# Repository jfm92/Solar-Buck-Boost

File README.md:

#Solar Buck-Boost

Li-Po charging module with CN3063 and TPS63020 for solar and USB power, ensures constant voltage and efficiency. By default it's configure to ouput 3.3v with power saving mode off.

**Important you can use a solar panel with a maximum of 6V and minimum of 4.4v, but it's recommendable to use 5V solar panel modules**

## Configuration:

This modules allows to set the output voltage an working mode by doing some little modifications.

## Output Voltage:

This module allows to set an ouput voltage by changing R4 resistor. By default it's 1M giving an ouput of 3.3v, but you can get the following ouput values.

| VOUT  |   R4   |
|-------|--------|
| 2.5V  | 750K   |
| 3.3V  | 1M     |
| 3.6V  | 1.1M   |
| 4.5V  | 1.43M  |
| 5V    | 1.6M   |

## Power saving mode:

- Power saving mode on: Join R8.
- Power saving mode off: Join R7.

## Schematics:

## PCB:

## Bill of materials:

You can find a list of material with a link to the crucial one.

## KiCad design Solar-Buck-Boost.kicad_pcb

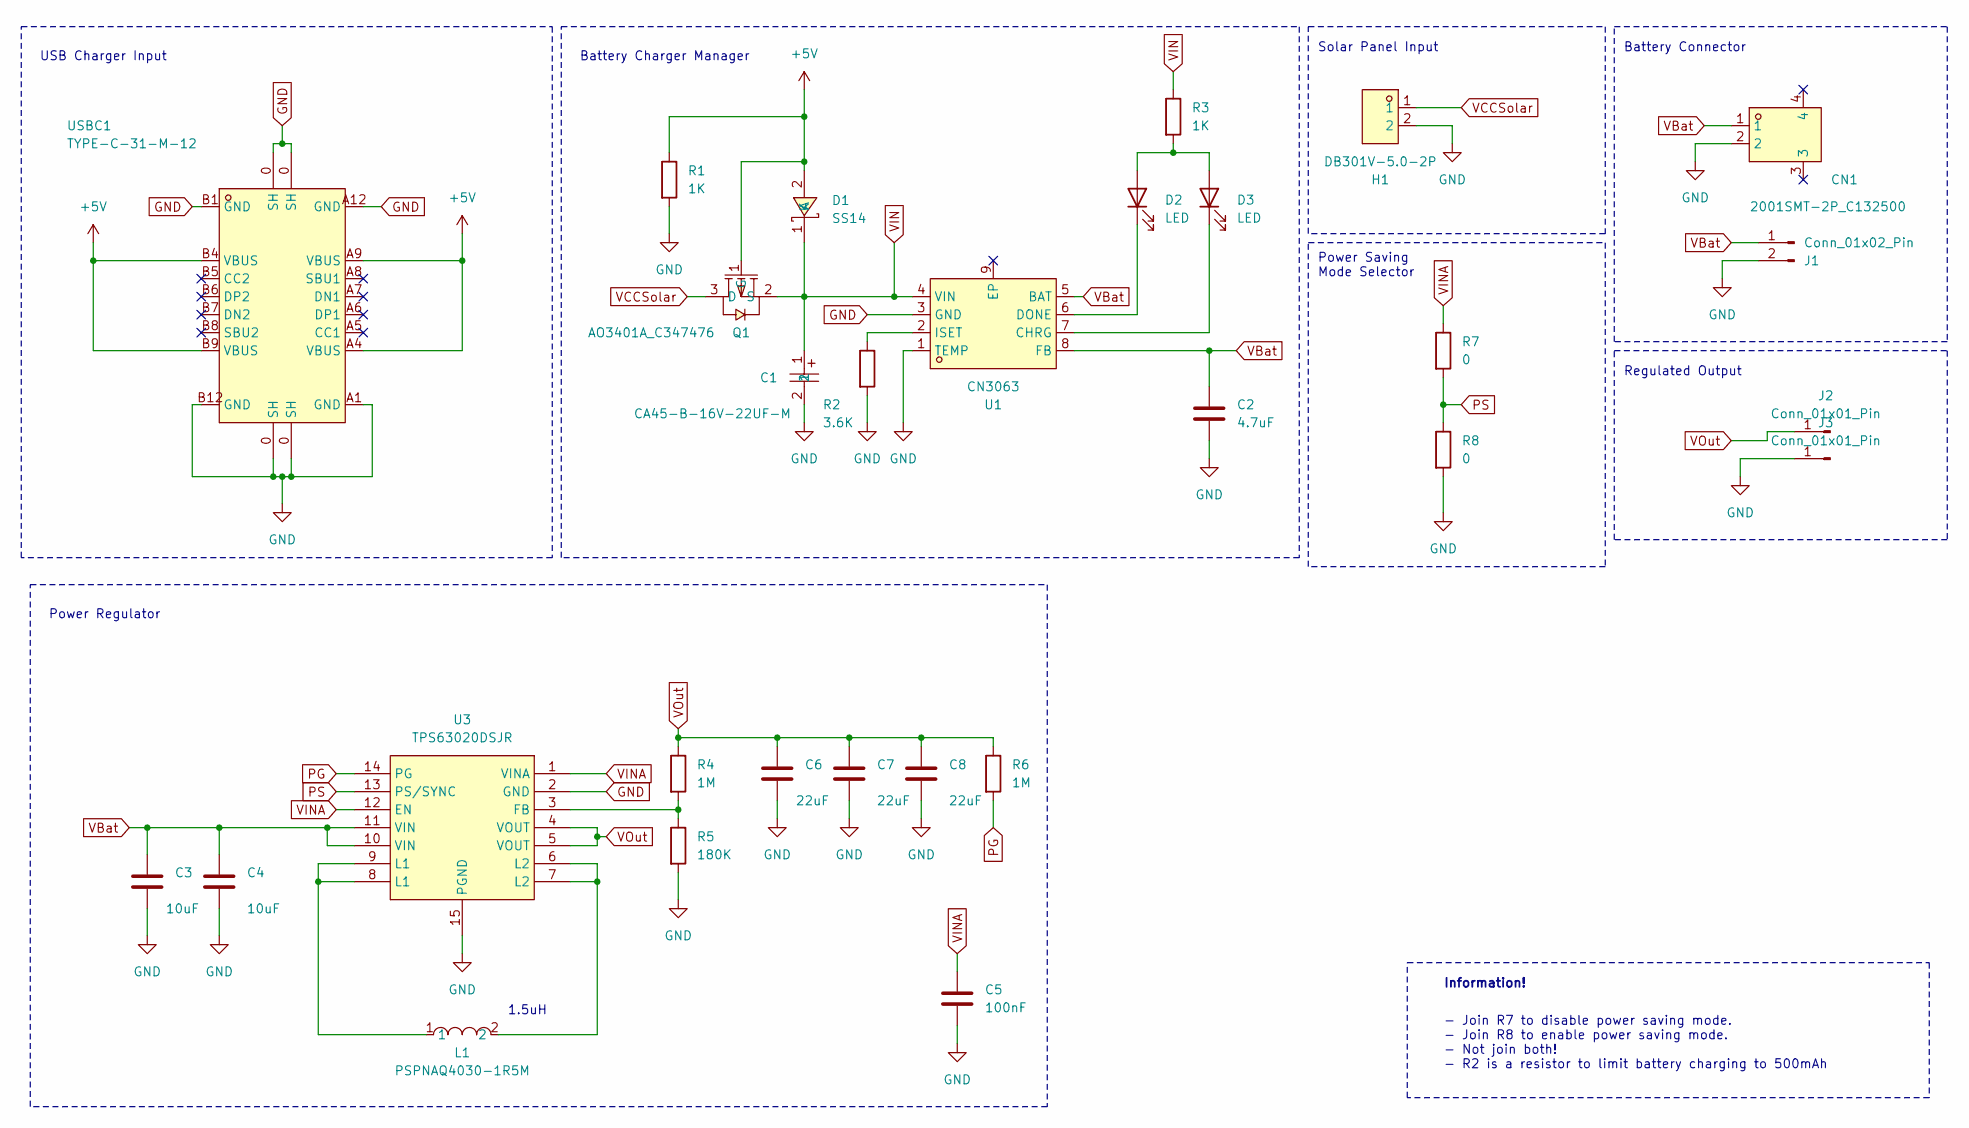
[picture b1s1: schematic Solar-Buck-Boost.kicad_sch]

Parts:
C1: CA45-B-16V-22UF-M; CAP-SMD_L3.5-W2.8-R-RD; LCSC Part C140371
C2: 4.7uF; C_0805_2012Metric
C3, C4: 10uF; C_0805_2012Metric
C5: 100nF; C_0603_1608Metric
C6, C7, C8: 22uF; C_0805_2012Metric
CN1: 2001SMT-2P_C132500; CONN-SMD_2001SMT-2P-WT; LCSC Part C132500
D1: SS14; SMA_L4.2-W2.6-LS5.3-RD; LCSC Part C2480
D2, D3: LED; LED_0805_2012Metric
H1: DB301V-5.0-2P; CONN-TH_2P-P5.00_L7.6-W10.0; LCSC Part C395882
J1: Conn_01x02_Pin; PinHeader_1x02_P2.54mm_Vertical
J2, J3: Conn_01x01_Pin; PinSocket_1x01_P2.54mm_Vertical
L1: PSPNAQ4030-1R5M; IND-SMD_L4.0-W4.0; LCSC Part C436670
Q1: AO3401A_C347476; SOT-23_L2.9-W1.3-P1.90-LS2.4-BR; LCSC Part C347476
R1, R3: 1K; R_0805_2012Metric
R2: 3.6K; R_0805_2012Metric
R4, R6: 1M; R_0805_2012Metric
R5: 180K; R_0805_2012Metric
R7, R8: 0; R_0402_1005Metric
U1: CN3063; SOIC-8_L4.9-W3.9-P1.27-LS6.0-BL-EP3.3-1; LCSC Part C28078
U3: TPS63020DSJR; VSON-14_L4.0-W3.0-P0.50-BL-EP_TI_DSJ; LCSC Part C15483
USBC1: TYPE-C-31-M-12; USB-C_SMD-TYPE-C-31-M-12; LCSC Part C165948

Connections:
+5V: D1.2 (A), Q1.1 (G), R1.1, USBC1.A4 (VBUS), USBC1.A9 (VBUS), USBC1.B4 (VBUS), USBC1.B9 (VBUS)
GND: C1.2, C2.2, C3.2, C4.2, C5.2, C6.2, C7.2, C8.2, CN1.2, H1.2, J1.2, J3.1, R1.2, R2.2, R5.2, R8.2, U1.1 (TEMP), U1.3 (GND), U3.2 (GND), U3.15 (PGND), USBC1.0 (SH), USBC1.A1 (GND), USBC1.A12 (GND), USBC1.B1 (GND), USBC1.B12 (GND)
unnamed: D2.2 (A), D3.2 (A), R3.2
unnamed: D2.1 (K), U1.6 (DONE)
unnamed: D3.1 (K), U1.7 (CHRG)
unnamed: L1.1, U3.8 (L1), U3.9 (L1)
unnamed: L1.2, U3.6 (L2), U3.7 (L2)
unnamed: R2.1, U1.2 (ISET)
unnamed: R4.2, R5.1, U3.3 (FB)
PG: R6.2, U3.14 (PG)
PS: R7.2, R8.1, U3.13 (PS/SYNC)
VBat: C2.1, C3.1, C4.1, CN1.1, J1.1, U1.5 (BAT), U1.8 (FB), U3.10 (VIN), U3.11 (VIN)
VCCSolar: H1.1, Q1.3 (D)
VIN: C1.1, D1.1 (K), Q1.2 (S), R3.1, U1.4 (VIN)
VINA: C5.1, R7.1, U3.1 (VINA), U3.12 (EN)
VOut: C6.1, C7.1, C8.1, J2.1, R4.1, R6.1, U3.4 (VOUT), U3.5 (VOUT)

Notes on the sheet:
Power Regulator
Battery Charger Manager
Regulated Output
USB Charger Input
Power Saving Mode Selector
- Join R7 to disable power saving mode. - Join R8 to enable power saving mode. - Not join both! - R2 is a resistor to limit battery charging to 500mAh
Information!
Battery Connector
1.5uH
Solar Panel Input

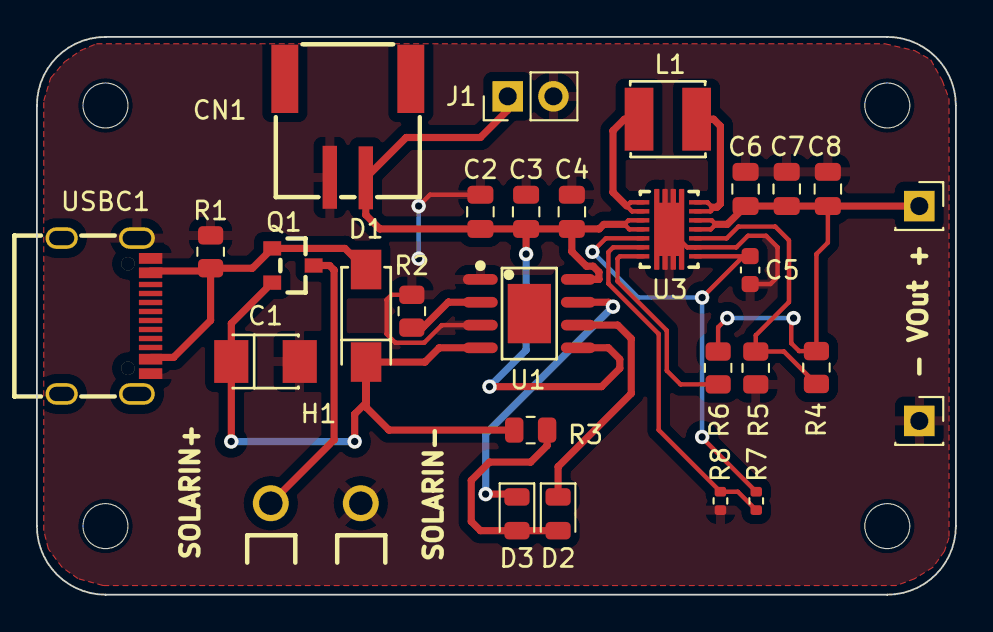
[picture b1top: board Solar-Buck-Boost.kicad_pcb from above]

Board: 2 copper layers, 51.1 x 31.0 mm, 29 parts (0 on the bottom side), 16 nets.

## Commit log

2023-12-11 Adding Solar-Buck Boots KiCad Project
2023-12-12 Schematics fix
2023-12-12 Adding schematics image
2023-12-20 Adding documentation
2023-12-28 Updating instructions with new picture
